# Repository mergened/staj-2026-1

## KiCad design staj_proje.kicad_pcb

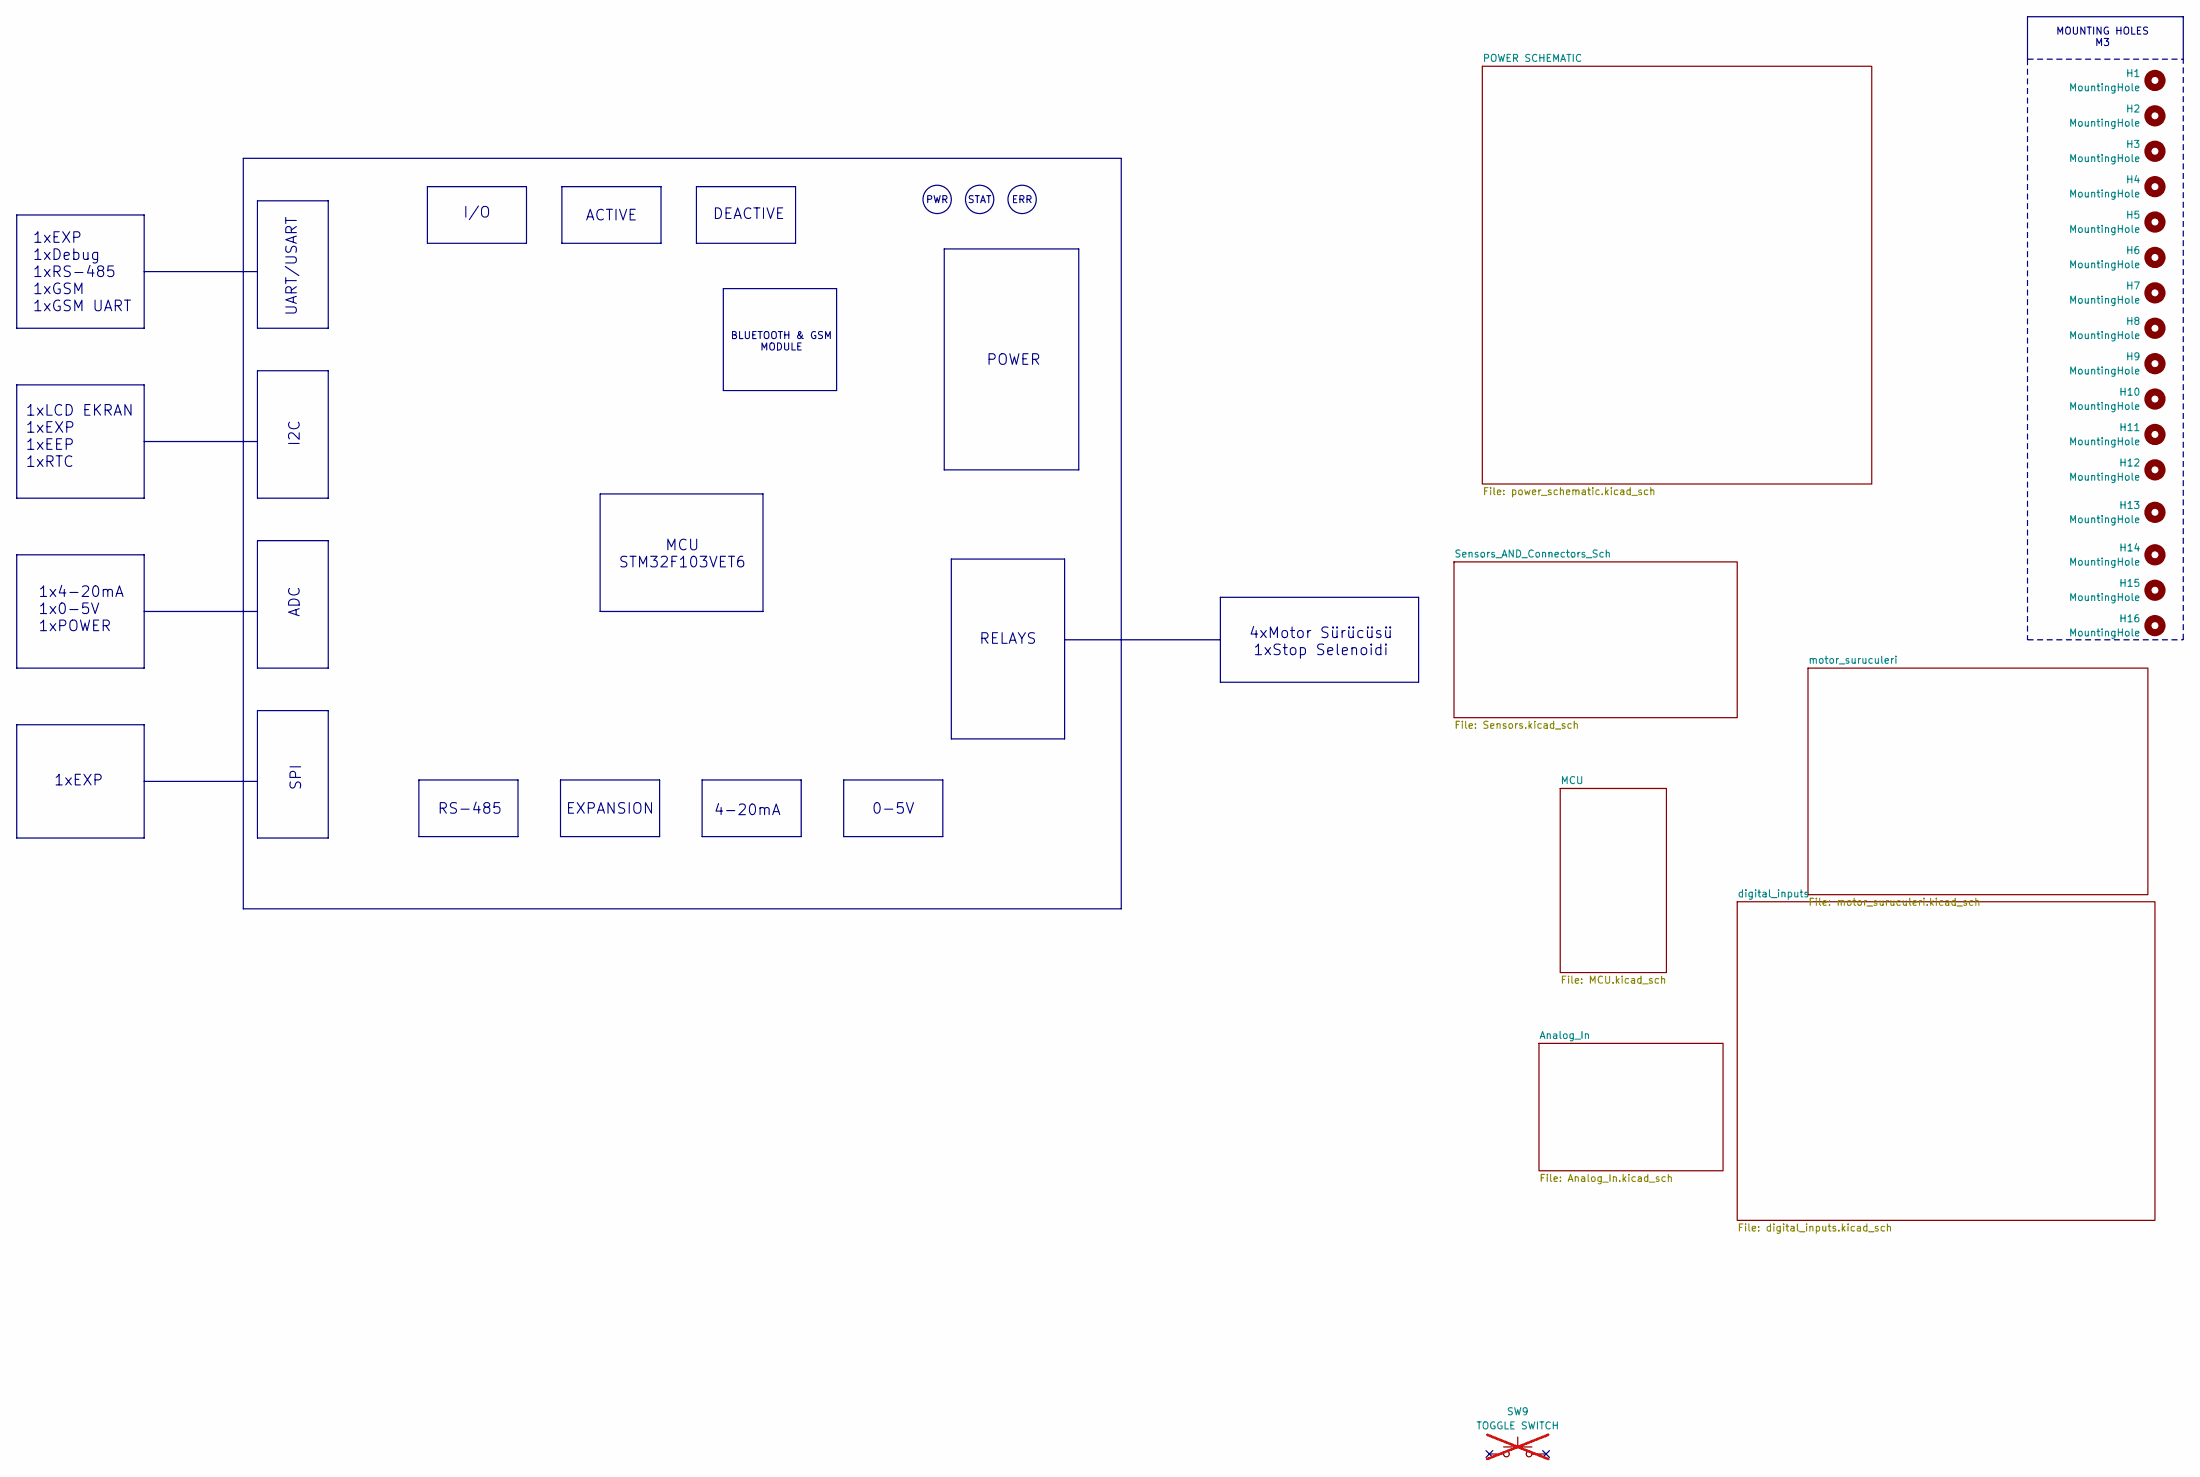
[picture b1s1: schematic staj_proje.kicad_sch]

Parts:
H1, H2, H3, H4, H5, H6, H7, H8, H9, H10, H11, H12: MountingHole; MountingHole_3.2mm_M3
H13, H14, H15, H16: MountingHole; MountingHole_2.7mm_M2.5
SW9: TOGGLE SWITCH; Manufacturer PN 100SP1T2B4M7QE; Digikey EG5419-ND; not fitted

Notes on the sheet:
ACTIVE
SPI
RELAYS
BLUETOOTH & GSM MODULE
1xLCD EKRAN 1xEXP 1xEEP 1xRTC
MOUNTING HOLES M3
ADC
UART/USART
STAT
DEACTIVE
1xEXP 1xDebug 1xRS-485 1xGSM 1xGSM UART
ERR
RS-485
PWR
MCU STM32F103VET6
4-20mA
POWER
0-5V
4xMotor Sürücüsü 1xStop Selenoidi
EXPANSION
I2C
1x4-20mA 1x0-5V 1xPOWER
I/O
1xEXP

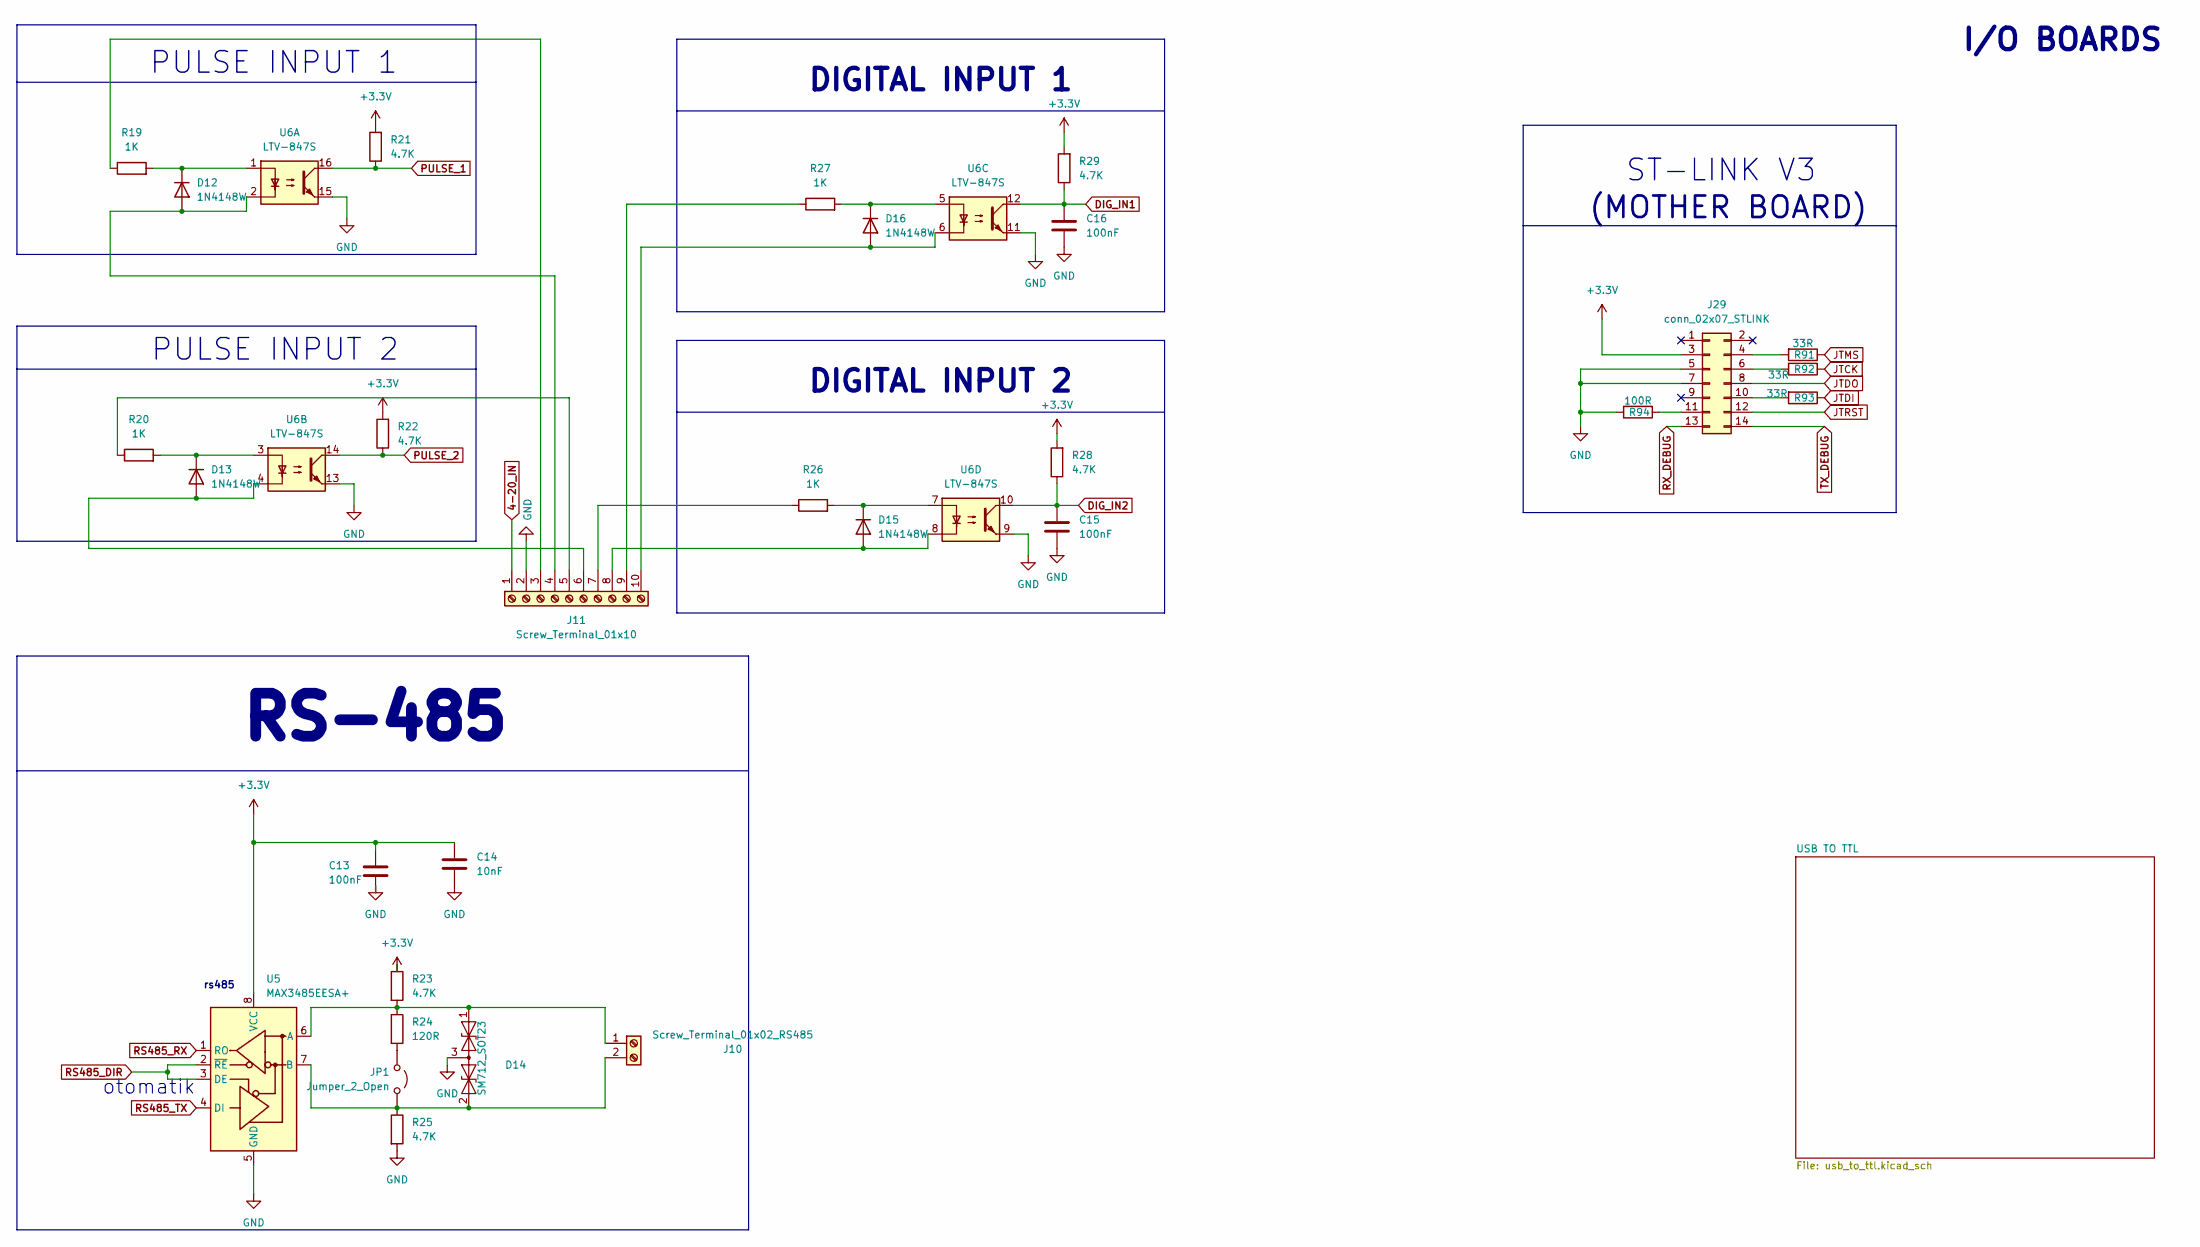
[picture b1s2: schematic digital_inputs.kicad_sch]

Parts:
C13, C15, C16: 100nF; C_0603_1608Metric; Manufacturer PN E0603X7R104K500NTD; Digikey 3372-E0603X7R104K500NTDTR-ND
C14: 10nF; C_0603_1608Metric; Manufacturer PN B0603C0G103J500NTD; Digikey 3372-B0603C0G103J500NTDTR-ND
D12, D13, D15, D16: 1N4148W; D_SOD-123; Manufacturer PN 1N4148W; Digikey 3372-1N4148WTR-ND
D14: SM712_SOT23; SOT-23-3; Manufacturer PN CDSOT23-SM712; Digikey CDSOT23-SM712CT-ND
J10: Screw_Terminal_01x02_RS485; PhoenixContact_MC_1,5_2-G-3.81_1x02_P3.81mm_Horizontal; Manufacturer PN 5444262; Digikey 277-11313-ND
J11: Screw_Terminal_01x10; PhoenixContact_MC_1,5_10-G-3.81_1x10_P3.81mm_Horizontal; Manufacturer PN 1803358; Digikey 277-1214-ND
J29: conn_02x07_STLINK; PinHeader_2x07_P1.27mm_Vertical_SMD; Manufacturer PN SAM13170CT-ND; Digikey FTSH-107-01-F-DV-K-P-TR
JP1: Jumper_2_Open; PinHeader_1x02_P2.54mm_Vertical; Manufacturer PN 61300211121; Digikey 732-5315-ND
R19, R20, R26, R27: 1K; R_0603_1608Metric; Manufacturer PN RMCF0603FT1K00; Digikey RMCF0603FT1K00CT-ND
R21, R22, R23, R25, R28, R29: 4.7K; R_0603_1608Metric; Manufacturer PN RC0603FR-074K7L; Digikey 311-4.70KHRCT-ND
R24: 120R; R_0603_1608Metric; Manufacturer PN RC0603FR-07120RL; Digikey 311-120HRCT-ND
R91, R92, R93: 33R; R_0603_1608Metric; Manufacturer PN ANTISULF RES0603 1% 0 OHM; Digikey 4713-CAS06F0000CT-ND
R94: 100R; R_0603_1608Metric; Manufacturer PN ANTISULF RES0603 1% 0 OHM; Digikey 4713-CAS06F0000CT-ND
U5: MAX3485EESA+; SOIC-8_3.9x4.9mm_P1.27mm; Manufacturer PN MAX3485EESA+; Digikey MAX3485EESA+-ND
U6: LTV-847S; SMDIP-16_W9.53mm; Manufacturer PN LTV-847S; Digikey 160-1371-5-ND

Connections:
4-20_IN: J11.1; also elsewhere on the board
+3.3V: C13.1, C14.1, J29.3, R21.2, R22.2, R23.1, R28.2, R29.2, U5.8 (VCC); also elsewhere on the board
DIG_IN1: C16.1, R29.1, U6.12; also elsewhere on the board
DIG_IN2: C15.1, R28.1, U6.10; also elsewhere on the board
GND: C13.2, C14.2, C15.2, C16.2, D14.3 (common), J11.2, J29.5, J29.7, R25.2, R94.2, U5.5 (GND), U6.9, U6.11, U6.13, U6.15; also elsewhere on the board
JTCK: R92.1; also elsewhere on the board
JTDI: R93.1; also elsewhere on the board
JTDO: J29.8; also elsewhere on the board
JTMS: R91.1; also elsewhere on the board
JTRST: J29.12; also elsewhere on the board
unnamed: D12.2 (A), J11.4, U6.2
unnamed: D12.1 (K), R19.2, U6.1
unnamed: D13.2 (A), J11.6, U6.4
unnamed: D13.1 (K), R20.2, U6.3
unnamed: D14.1 (A1), J10.1, R23.2, R24.1, U5.6 (A)
unnamed: D14.2 (A2), J10.2, JP1.1 (A), R25.1, U5.7 (B)
unnamed: D15.2 (A), J11.8, U6.8
unnamed: D15.1 (K), R26.2, U6.7
unnamed: D16.2 (A), J11.10, U6.6
unnamed: D16.1 (K), R27.2, U6.5
unnamed: J11.3, R19.1
unnamed: J11.5, R20.1
unnamed: J11.7, R26.1
unnamed: J11.9, R27.1
unnamed: J29.4, R91.2
unnamed: J29.6, R92.2
unnamed: J29.10, R93.2
unnamed: J29.11, R94.1
unnamed: JP1.2 (B), R24.2
PULSE_1: R21.1, U6.16; also elsewhere on the board
PULSE_2: R22.1, U6.14; also elsewhere on the board
RS485_DIR: U5.2 (~RE), U5.3 (DE); also elsewhere on the board
RS485_RX: U5.1 (RO); also elsewhere on the board
RS485_TX: U5.4 (DI); also elsewhere on the board
RX_DEBUG: J29.13; also elsewhere on the board
TX_DEBUG: J29.14; also elsewhere on the board

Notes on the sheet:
DIGITAL INPUT 2
I/O BOARDS
ST-LINK V3
RS-485
PULSE INPUT 2
(MOTHER BOARD)
PULSE INPUT 1
rs485
DIGITAL INPUT 1
otomatik

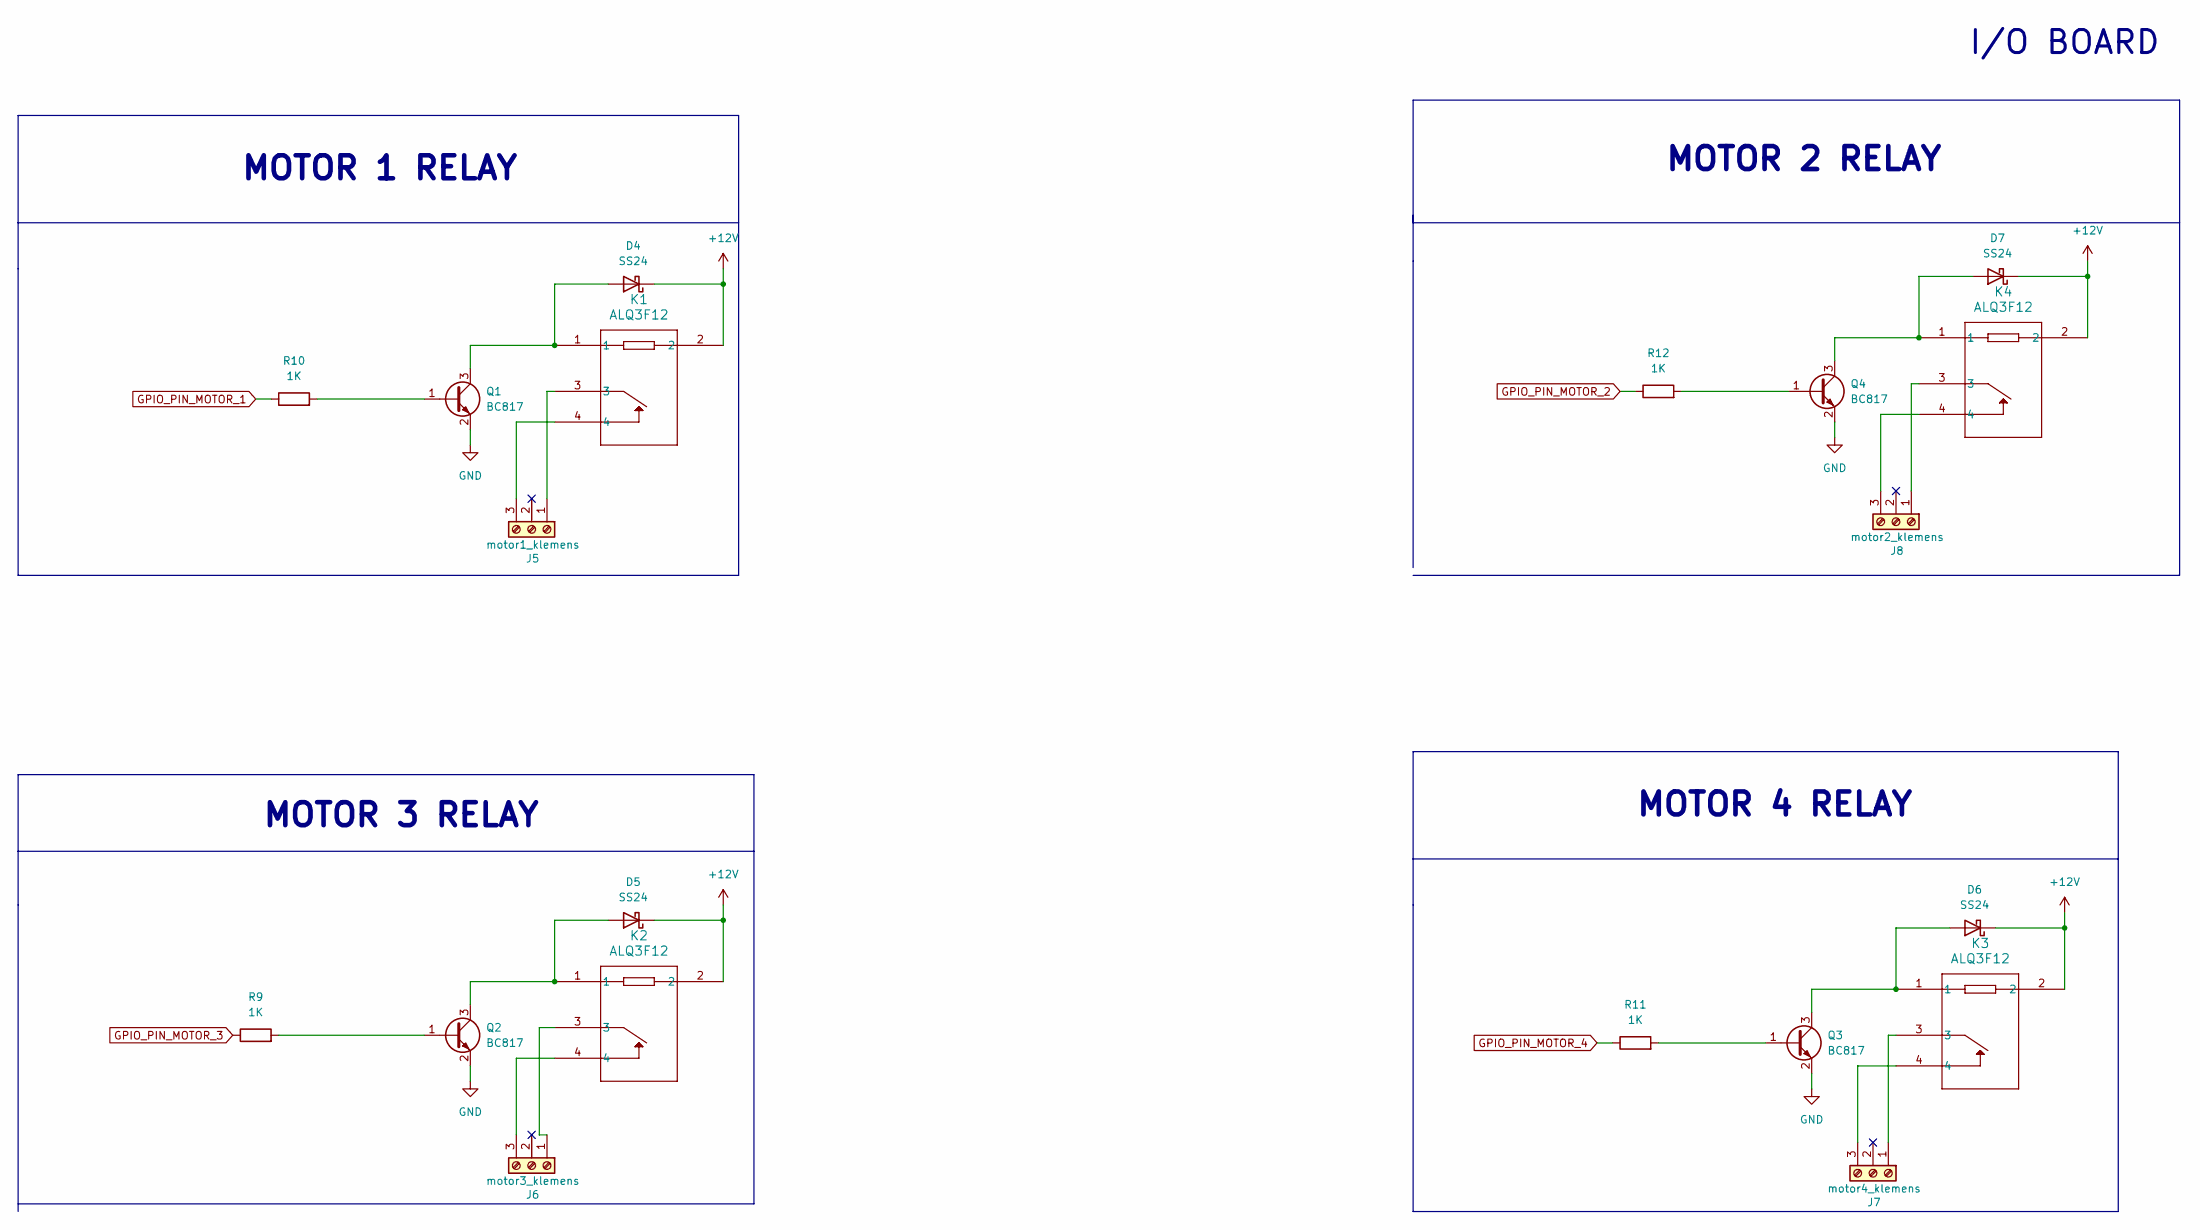
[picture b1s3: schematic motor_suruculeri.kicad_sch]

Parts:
D4, D5, D6, D7: SS24; D_SMB; Manufacturer PN SS24; Digikey 1801-SS24CT-ND
J5: motor1_klemens; PhoenixContact_MC_1,5_3-G-5.08_1x03_P5.08mm_Horizontal; Manufacturer PN 1803280; Digikey 277-1207-ND
J6: motor3_klemens; PhoenixContact_MC_1,5_3-G-5.08_1x03_P5.08mm_Horizontal; Manufacturer PN 1803280; Digikey 277-1207-ND
J7: motor4_klemens; PhoenixContact_MC_1,5_3-G-5.08_1x03_P5.08mm_Horizontal; Manufacturer PN 1803280; Digikey 277-1207-ND
J8: motor2_klemens; PhoenixContact_MC_1,5_3-G-5.08_1x03_P5.08mm_Horizontal; Manufacturer PN 1803280; Digikey 277-1207-ND
K1, K2, K3, K4: ALQ3F12; Manufacturer PN ALQ3F12; Digikey 255-5407-ND
Q1, Q2, Q3, Q4: BC817; SOT-23-3; Manufacturer PN BC817-16-7; Digikey BC817-16-7-ND
R9, R10, R11, R12: 1K; R_0603_1608Metric; Manufacturer PN RC0603FR-071KL; Digikey 311-1.00KHRCT-ND

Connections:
+12V: D4.1 (K), D5.1 (K), D6.1 (K), D7.1 (K), K1.2, K2.2, K3.2, K4.2; also elsewhere on the board
GND: Q1.2 (E), Q2.2 (E), Q3.2 (E), Q4.2 (E); also elsewhere on the board
GPIO_PIN_MOTOR_1: R10.1; also elsewhere on the board
GPIO_PIN_MOTOR_2: R12.1; also elsewhere on the board
GPIO_PIN_MOTOR_3: R9.1; also elsewhere on the board
GPIO_PIN_MOTOR_4: R11.1; also elsewhere on the board
unnamed: D4.2 (A), K1.1, Q1.3 (C)
unnamed: D5.2 (A), K2.1, Q2.3 (C)
unnamed: D6.2 (A), K3.1, Q3.3 (C)
unnamed: D7.2 (A), K4.1, Q4.3 (C)
unnamed: J5.1, K1.3
unnamed: J5.3, K1.4
unnamed: J6.1, K2.3
unnamed: J6.3, K2.4
unnamed: J7.1, K3.3
unnamed: J7.3, K3.4
unnamed: J8.1, K4.3
unnamed: J8.3, K4.4
unnamed: Q1.1 (B), R10.2
unnamed: Q2.1 (B), R9.2
unnamed: Q3.1 (B), R11.2
unnamed: Q4.1 (B), R12.2

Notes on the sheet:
I/O BOARD
MOTOR 3 RELAY
MOTOR 4 RELAY
MOTOR 2 RELAY
MOTOR 1 RELAY

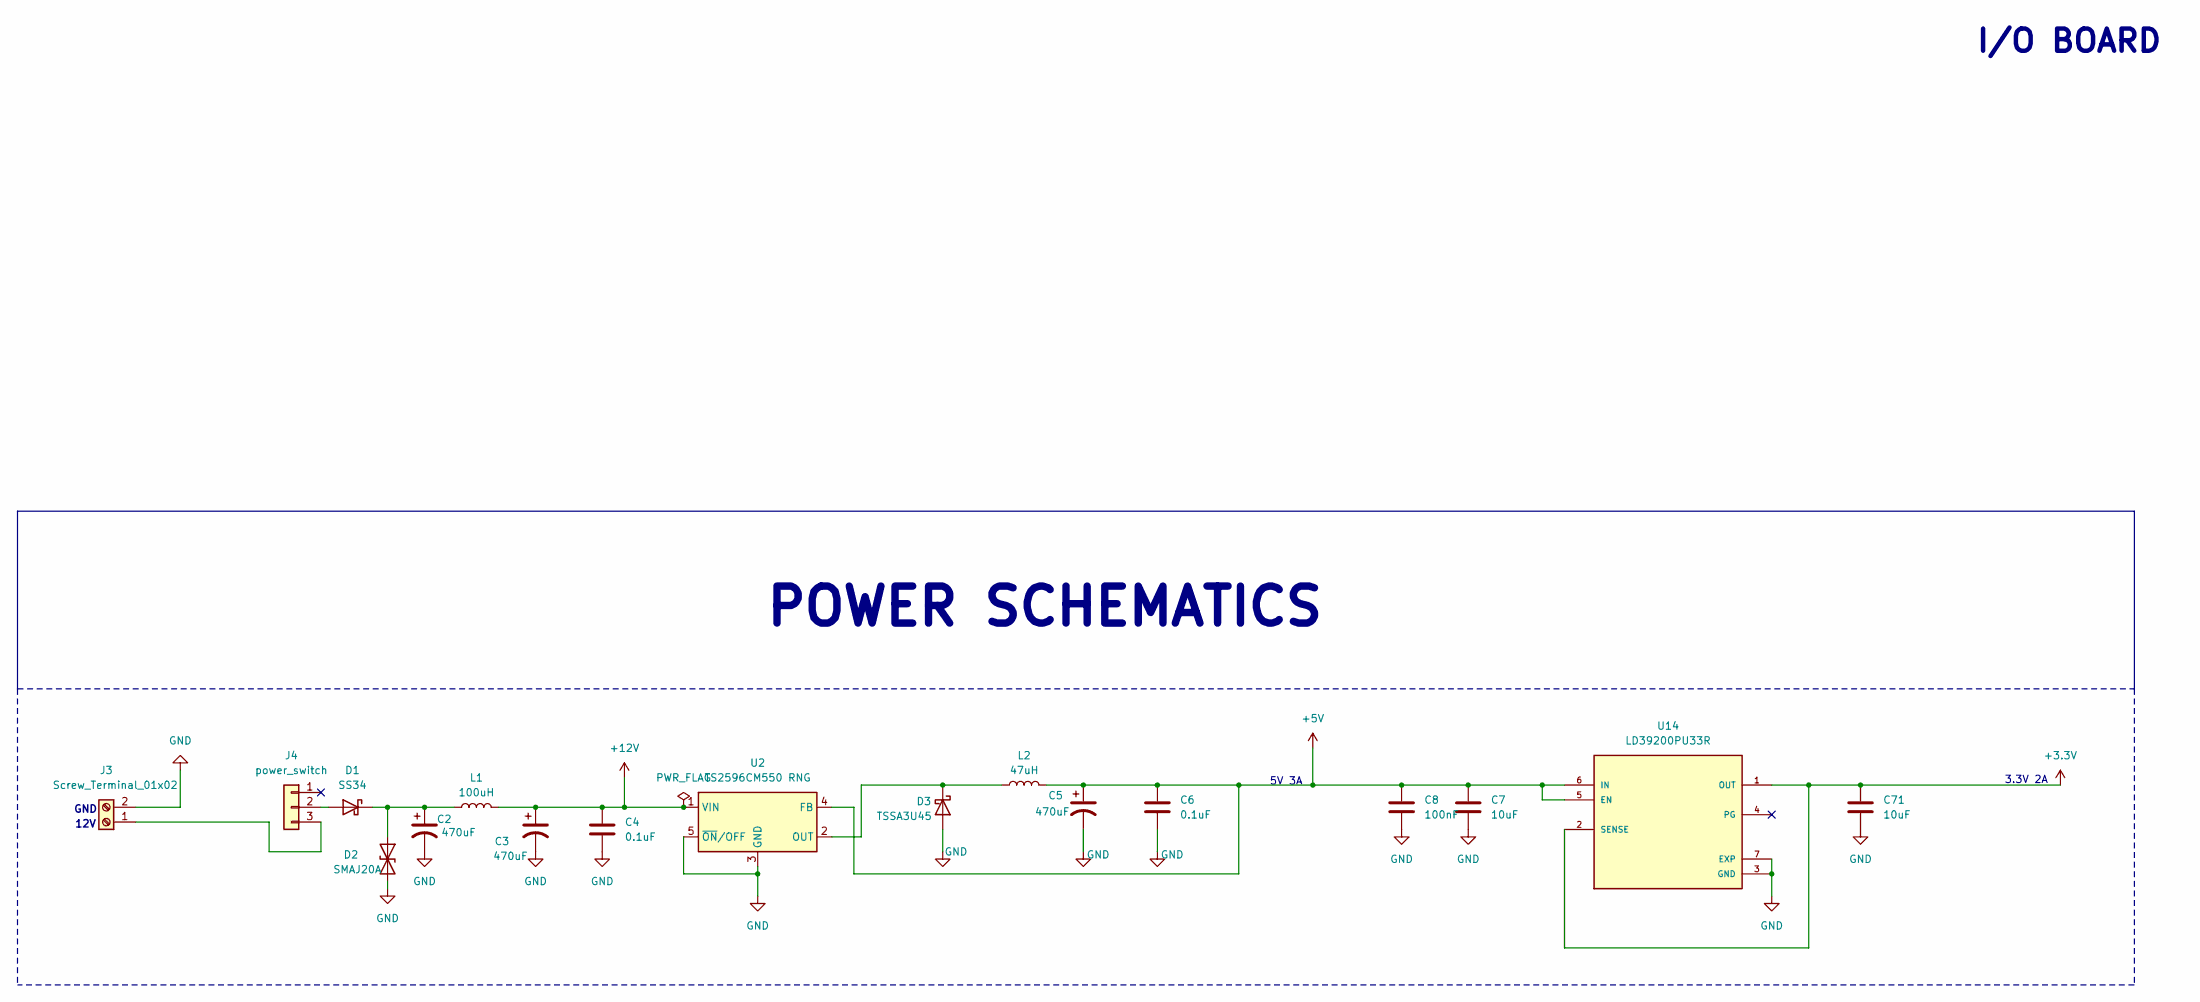
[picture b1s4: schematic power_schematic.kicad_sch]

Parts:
C2, C3, C5: 470uF; CP_Radial_D10.0mm_P5.00mm; Manufacturer PN 50ZLJ470M10X20; Digikey 1189-50ZLJ470M10X20-ND
C4, C6: 0.1uF; C_0603_1608Metric; Manufacturer PN C0603C104K5RACTU; Digikey 399-C0603C104K5RACTUCT-ND
C7, C71: 10uF; C_0805_2012Metric; Manufacturer PN 08056D106KAT2A; Digikey 478-KGM21AR50J106KUCT-ND
C8: 100nF; C_0603_1608Metric; Manufacturer PN C0603C104K5RACTU; Digikey 399-C0603C104K5RACTUCT-ND
D1: SS34; D_SMC; Manufacturer PN SS34; Digikey SS34FSCT-ND
D2: SMAJ20A; D_SMA; Manufacturer PN SMAJ20A; Digikey SMAJ20ALFCT-ND
D3: TSSA3U45; D_SMA; Manufacturer PN TSSA3U45; Digikey 1801-TSSA3U45CT-ND
J3: Screw_Terminal_01x02; PhoenixContact_MC_1,5_2-G-5.08_1x02_P5.08mm_Horizontal; Manufacturer PN 1715721; Digikey 277-1263-ND
J4: power_switch; JST_EH_B3B-EH-A_1x03_P2.50mm_Vertical; Manufacturer PN B3B-EH-A; Digikey 455-B3B-EH-A-ND
L1: 100uH; L_0603_1608Metric; Manufacturer PN SDR0603-101KL; Digikey 118-SDR0603-101KLCT-ND
L2: 47uH; L_12x12mm_H8mm; Manufacturer PN CDRH127/LDNP-470MC; Digikey 308-1339-1-ND
U2: TS2596CM550 RNG; TO-263-5_TabPin3; Manufacturer PN TS2596CM550 RNG; Digikey TS2596CM550RNGCT-ND
U14: LD39200PU33R; PARTREV 3; Digikey 497-15229-1-ND

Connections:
+3.3V: C71.1, U14.1 (OUT), U14.2 (SENSE); also elsewhere on the board
+5V: C5.1, C6.1, C7.1, C8.1, L2.2, U2.4 (FB), U14.5 (EN), U14.6 (IN); also elsewhere on the board
+12V: C3.1, C4.1, L1.2, U2.1 (VIN); also elsewhere on the board
GND: C2.2, C3.2, C4.2, C5.2, C6.2, C7.2, C8.2, C71.2, D2.2 (A2), D3.2 (A), J3.2, U2.3 (GND), U2.5 (~ON/OFF), U14.3 (GND), U14.7 (EXP); also elsewhere on the board
unnamed: D1.2 (A), J4.2
unnamed: C2.1, D1.1 (K), D2.1 (A1), L1.1
unnamed: D3.1 (K), L2.1, U2.2 (OUT)
unnamed: J3.1, J4.3

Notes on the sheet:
POWER SCHEMATICS
I/O BOARD
5V 3A
12V
3.3V 2A
GND

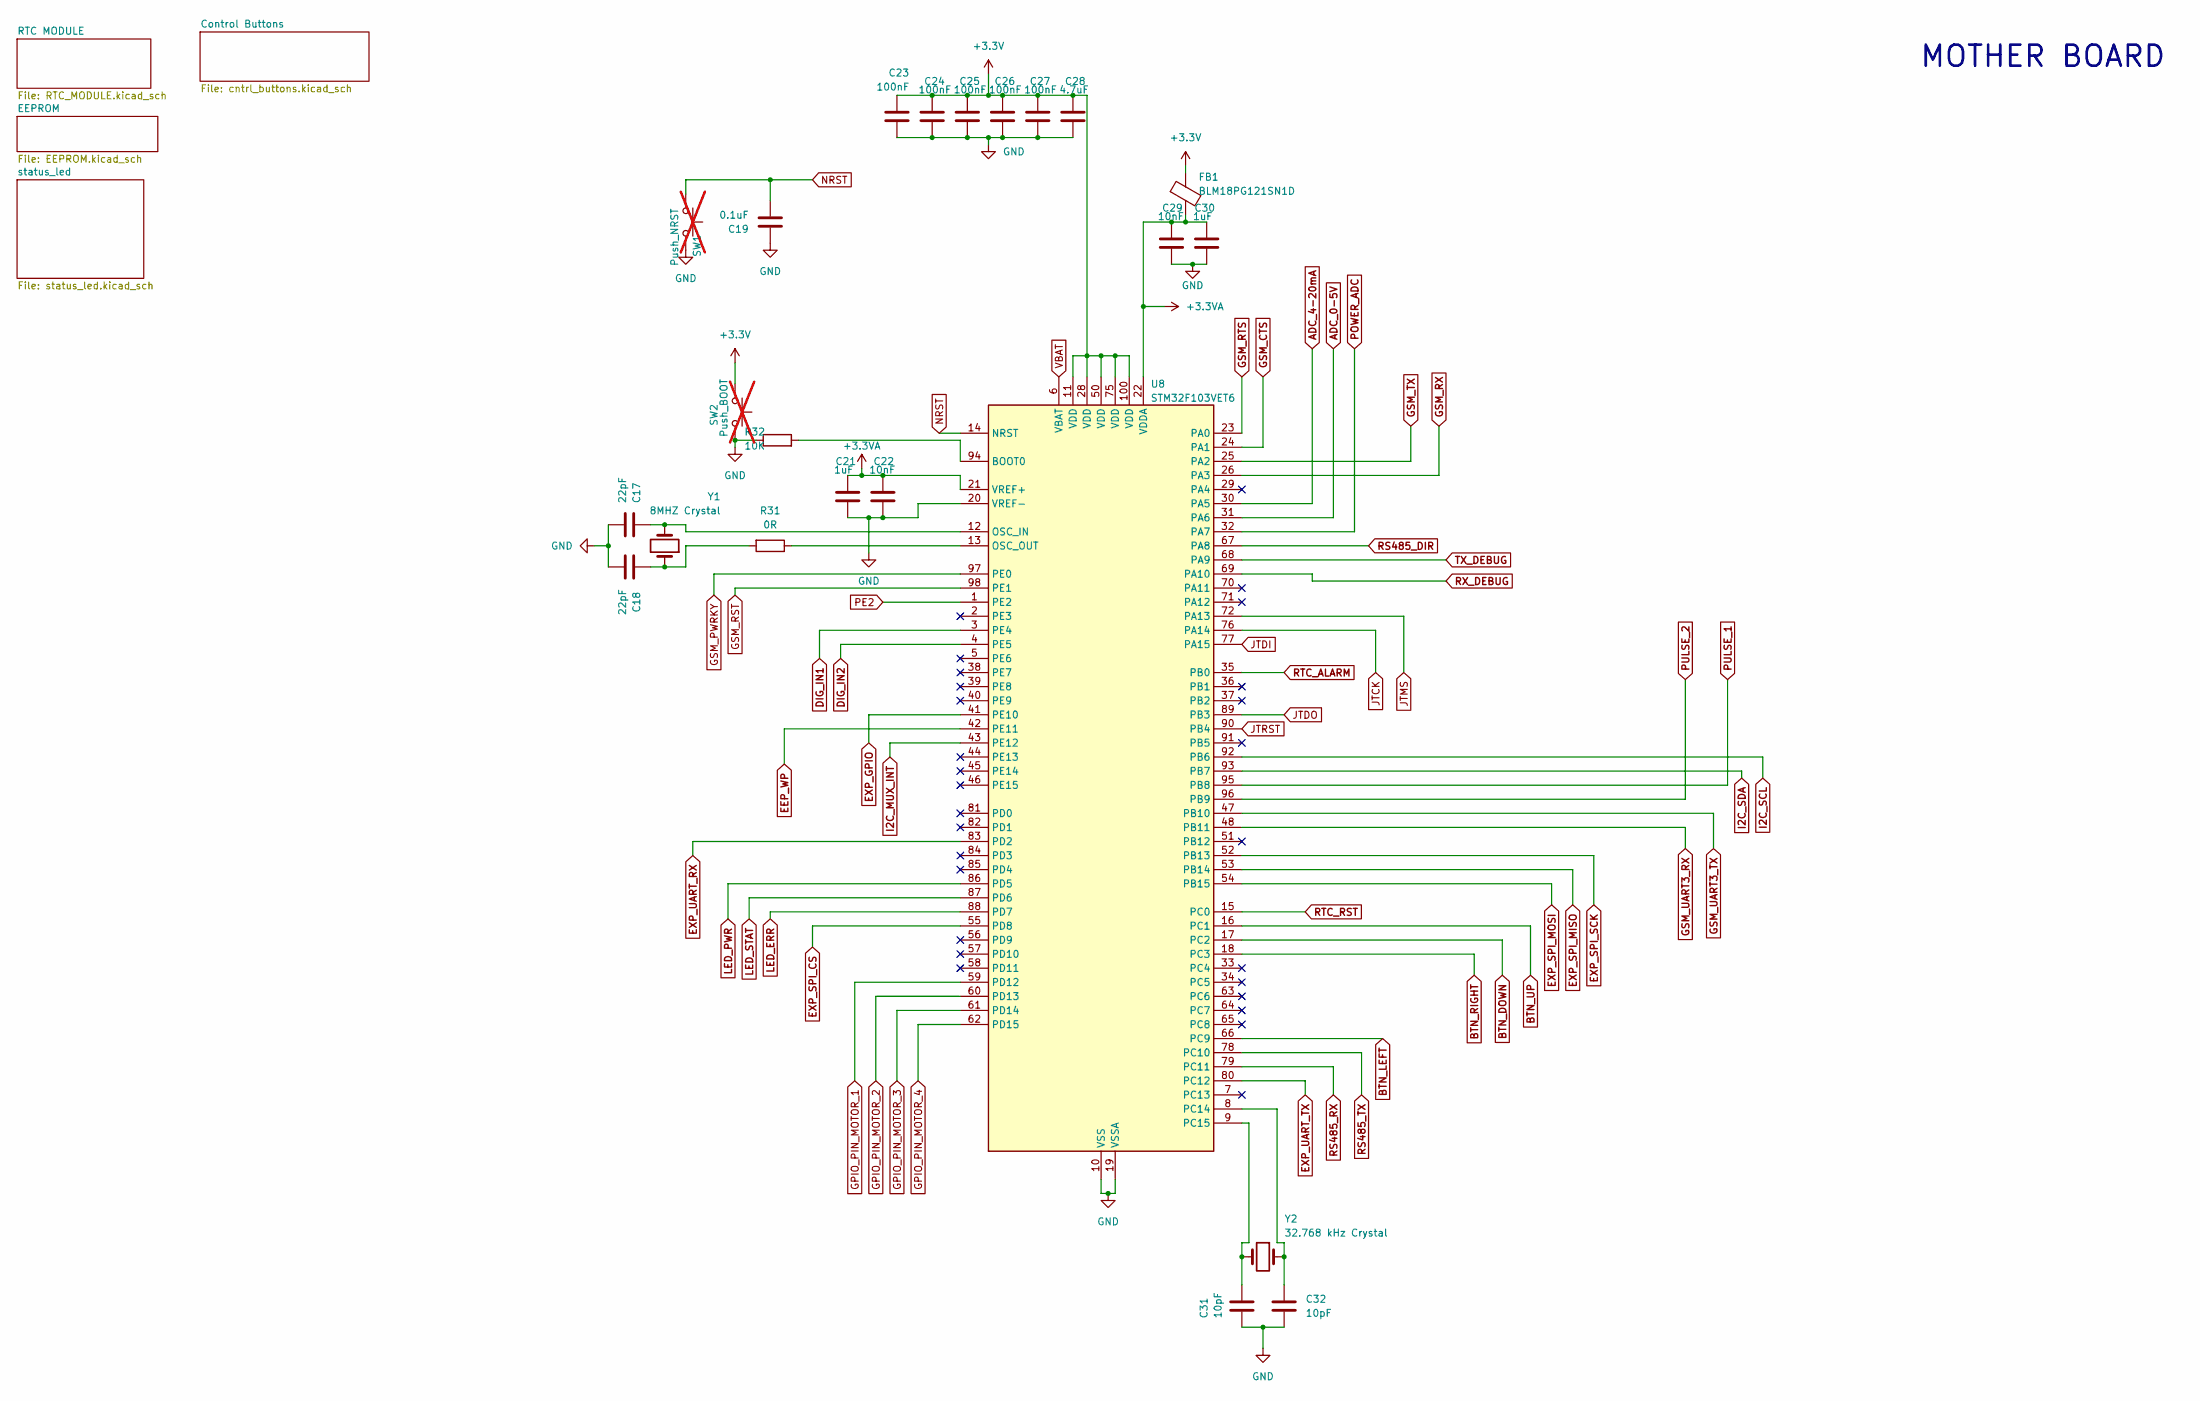
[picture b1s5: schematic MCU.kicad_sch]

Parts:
C17, C18: 22pF; C_0603_1608Metric; Manufacturer PN GMC10CG220K50NT; Digikey 2571-GMC10CG220K50NTTR-ND
C19: 0.1uF; C_0603_1608Metric; Manufacturer PN C0603C104K5RACTU; Digikey 399-C0603C104K5RACTUCT-ND
C21, C30: 1uF; C_0603_1608Metric; Manufacturer PN GMC10X5R105M50NT; Digikey 2571-GMC10X5R105M50NTTR-ND
C22, C29: 10nF; C_0603_1608Metric; Manufacturer PN B0603C0G103J500NTD; Digikey 3372-B0603C0G103J500NTDTR-ND
C23, C24, C25, C26, C27: 100nF; C_0603_1608Metric; Manufacturer PN E0603X7R104K500NTD; Digikey 3372-E0603X7R104K500NTDTR-ND
C28: 4.7uF; C_0603_1608Metric; Manufacturer PN GMC10X5R475K25NT; Digikey 2571-GMC10X5R475K25NTTR-ND
C31, C32: 10pF; C_0603_1608Metric; Manufacturer PN C0603C100K5GACTU; Digikey 399-C0603C100K5GACTUCT-ND
FB1: BLM18PG121SN1D; C_0805_2012Metric; Manufacturer PN BLM18PG121SN1D; Digikey 490-1037-1-ND
R31: 0R; R_0603_1608Metric; Manufacturer PN ANTISULF RES0603 1% 0 OHM; Digikey 4713-CAS06F0000CT-ND
R32: 10K; R_0603_1608Metric; Manufacturer PN RC0603FR-0710KL; Digikey 311-10.0KHRCT-ND
SW1: Push_NRST; SW_PUSH_6mm; Manufacturer PN B3FS-1002P; Digikey SW424CT-ND; not fitted
SW2: Push_BOOT; SW_PUSH_6mm; Manufacturer PN B3FS-1002P; Digikey SW424CT-ND; not fitted
U8: STM32F103VET6; LQFP-100-1EP_14x14mm_P0.5mm_EP6.9x6.9mm; Manufucturer PN STM32F103VET6; Digikey 497-6443-ND
Y1: 8MHZ Crystal; Crystal_SMD_3215-2Pin_3.2x1.5mm; Manufacturer PN ABM3B-8.000MHZ-10-1-U-T; Digikey 535-9721-1-ND
Y2: 32.768 kHz Crystal; Crystal_SMD_5032-2Pin_5.0x3.2mm; Manufacturer PN ABS07-32.768KHZ-7-T; Digikey 535-9543-1-ND

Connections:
+3.3V: C23.1, C24.1, C25.1, C26.1, C27.1, C28.1, FB1.1, SW2.2, U8.11 (VDD), U8.28 (VDD), U8.50 (VDD), U8.75 (VDD), U8.100 (VDD); also elsewhere on the board
+3.3VA: C21.1, C22.1, C29.1, C30.1, FB1.2, U8.21 (VREF+), U8.22 (VDDA); also elsewhere on the board
ADC_0-5V: U8.31 (PA6); also elsewhere on the board
ADC_4-20mA: U8.30 (PA5); also elsewhere on the board
BTN_DOWN: U8.17 (PC2); also elsewhere on the board
BTN_LEFT: U8.66 (PC9); also elsewhere on the board
BTN_RIGHT: U8.18 (PC3); also elsewhere on the board
BTN_UP: U8.16 (PC1); also elsewhere on the board
DIG_IN1: U8.3 (PE4); also elsewhere on the board
DIG_IN2: U8.4 (PE5); also elsewhere on the board
EEP_WP: U8.42 (PE11); also elsewhere on the board
EXP_GPIO: U8.41 (PE10); also elsewhere on the board
EXP_SPI_CS: U8.55 (PD8); also elsewhere on the board
EXP_SPI_MISO: U8.53 (PB14); also elsewhere on the board
EXP_SPI_MOSI: U8.54 (PB15); also elsewhere on the board
EXP_SPI_SCK: U8.52 (PB13); also elsewhere on the board
EXP_UART_RX: U8.83 (PD2); also elsewhere on the board
EXP_UART_TX: U8.80 (PC12); also elsewhere on the board
GND: C17.2, C18.1, C19.1, C21.2, C22.2, C23.2, C24.2, C25.2, C26.2, C27.2, C28.2, C29.2, C30.2, C31.1, C32.1, R32.1, SW1.1, SW2.1, U8.10 (VSS), U8.19 (VSSA), U8.20 (VREF-), U8.27 (VSS), U8.49 (VSS), U8.74 (VSS), U8.99 (VSS); also elsewhere on the board
GPIO_PIN_MOTOR_1: U8.59 (PD12); also elsewhere on the board
GPIO_PIN_MOTOR_2: U8.60 (PD13); also elsewhere on the board
GPIO_PIN_MOTOR_3: U8.61 (PD14); also elsewhere on the board
GPIO_PIN_MOTOR_4: U8.62 (PD15); also elsewhere on the board
GSM_CTS: U8.24 (PA1); also elsewhere on the board
GSM_PWRKY: U8.97 (PE0); also elsewhere on the board
GSM_RST: U8.98 (PE1); also elsewhere on the board
GSM_RTS: U8.23 (PA0); also elsewhere on the board
GSM_RX: U8.26 (PA3); also elsewhere on the board
GSM_TX: U8.25 (PA2); also elsewhere on the board
GSM_UART3_RX: U8.48 (PB11); also elsewhere on the board
GSM_UART3_TX: U8.47 (PB10); also elsewhere on the board
I2C_MUX_INT: U8.43 (PE12); also elsewhere on the board
I2C_SCL: U8.92 (PB6); also elsewhere on the board
I2C_SDA: U8.93 (PB7); also elsewhere on the board
JTCK: U8.76 (PA14); also elsewhere on the board
JTDI: U8.77 (PA15); also elsewhere on the board
JTDO: U8.89 (PB3); also elsewhere on the board
JTMS: U8.72 (PA13); also elsewhere on the board
JTRST: U8.90 (PB4); also elsewhere on the board
LED_ERR: U8.88 (PD7); also elsewhere on the board
LED_PWR: U8.86 (PD5); also elsewhere on the board
LED_STAT: U8.87 (PD6); also elsewhere on the board
NRST: C19.2, SW1.2, U8.14 (NRST)
unnamed: C18.2, R31.2, Y1.1
unnamed: R32.2, U8.94 (BOOT0)
unnamed: C17.1, U8.12 (OSC_IN), Y1.2
unnamed: R31.1, U8.13 (OSC_OUT)
unnamed: C32.2, U8.8 (PC14), Y2.1
unnamed: C31.2, U8.9 (PC15), Y2.2
PE2: U8.1 (PE2); also elsewhere on the board
POWER_ADC: U8.32 (PA7); also elsewhere on the board
PULSE_1: U8.95 (PB8); also elsewhere on the board
PULSE_2: U8.96 (PB9); also elsewhere on the board
RS485_DIR: U8.67 (PA8); also elsewhere on the board
RS485_RX: U8.79 (PC11); also elsewhere on the board
RS485_TX: U8.78 (PC10); also elsewhere on the board
RTC_ALARM: U8.35 (PB0); also elsewhere on the board
RTC_RST: U8.15 (PC0); also elsewhere on the board
RX_DEBUG: U8.69 (PA10); also elsewhere on the board
TX_DEBUG: U8.68 (PA9); also elsewhere on the board
VBAT: U8.6 (VBAT); also elsewhere on the board

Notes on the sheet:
MOTHER BOARD
